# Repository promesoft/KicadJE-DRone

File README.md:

# Kicad-droneosc
This is a very simple circuit based around S9018 NPN BJT's.

It creates a saw pulse and in this config I can modulate them via the base of the BJT. Its inspired by the work of [Kerry Wong](http://www.kerrywong.com/2014/03/19/bjt-in-reverse-avalanche-mode/) and [Sam Battle](https://www.lookmumnocomputer.com/projects/#/simplest-oscillator/)

## Reverse Avalanche Breakdown
As this oscilator is based on reverse avalanche breakdown it is highly dependent on the type of BJT used. For this setup the SS9018 high frequency transistor has been selected as it start oscilating below 9V (which is often used in stomp box effect pedals). 
For more details on this oscilator visit [AN47](https://www.analog.com/media/en/technical-documentation/application-notes/an47fa.pdf)

## Status - Rev A board - initial verification
### Initial 
| Stage  | Detail | Status |
| ------------- | ------------- | ------------- |
| create material  | sch/pcb | produced Rev A  |
| | gerber | produced and uploaded RevA |
| production  | ordered  | OK |
|  | produced | OK |
|  | delivered | OK |
### Preliminary validation
| Test  | Detail | Status |
| ------------- | ------------- | ------------- |
| Initial Inspection | Visual | See Errata |
| | Component Mounting | OK LFO 2|
| Initial Technical Test | LFO 1 |  |
| | OSC 1 |  |
| | LFO 2 | OK |
| | OSC 1 |  |

### Secondary validation
| Test  | Detail | Status |
| ------------- | ------------- |------------- |
| Product Test | LFO 1 |  |
| | OSC 1 |  |
| | LFO 2  | OSC+AM OK - Volume ok (see Errata)|
| | OSC 1 |  |
| Physical | 1590 II Box |  |
|  | Eurorack |  |
| Long Term Product Test | | ongoing |
### Errata
 - Footprint of mini jacks should be updated
 - Assisting text on potmeters
 - D1 is 0805 - should have been SOD123 or Minimelf
 - RV7 Volume Pot is reversed (possibly all other vol pots)
 - 10uf used for LFO output capacitor
  
### Issues and Notes

## Physical Construction
 - 50,8x100,2mm
 - Optional cut in 2 
 - Mounting in either Eurorack or Stompbox 1590B

## Vital Components
 - Jack connectors: PJ-321 (important for the footprint)
 - SS9018 HJ NPN BJT for the oscillator (important for the voltage)
 - 5516 LDR for the vactrol (matched with the pot for the osc)

## Features
4 Separate saw oscillators.
 - 2 identical
 - 1 simple
 - 1 with VCO (Vactrol) and Modulation input

## Modulation
### AM
Each section of the oscilators are AC coupled with a reasonably high input resistance that in the prototype enabled cascading of the oscilators so the output of the oscilator would be AM mulated with the input on the base.
### CV / FM / Vactrol
Prototype has been performed with a GL5516 LDR in a heat shrink package with an LED - its not exactly 1V/Oct but it works

# Prototype implementation
A simple stripboard implementation in a 1590B stompbox

# 3D 
Visualization of the board

## LFO 1 and OSC 1 3D

# LFO 1 Schematic

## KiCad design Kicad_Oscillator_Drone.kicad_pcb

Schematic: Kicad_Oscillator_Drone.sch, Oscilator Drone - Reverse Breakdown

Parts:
C1: 100u; CP_Radial_D6.3mm_P2.50mm
C2, C8: 680n; C_0805_2012Metric_Pad1.15x1.40mm_HandSolder
C3: 220u; CP_Radial_D7.5mm_P2.50mm
C4, C10: 470n; C_0805_2012Metric_Pad1.15x1.40mm_HandSolder
C5, C11: 220n; C_0805_2012Metric_Pad1.15x1.40mm_HandSolder
C6: 4u7; C_0805_2012Metric_Pad1.15x1.40mm_HandSolder
C7, C13: 1u; C_0805_2012Metric_Pad1.15x1.40mm_HandSolder
C9: 100u; CP_Radial_D7.5mm_P2.50mm
C12: 2u2; C_0805_2012Metric_Pad1.15x1.40mm_HandSolder
D1: 9v; D_0805_2012Metric_Pad1.15x1.40mm_HandSolder
D2: red; LED_D3.0mm
D3: OSC1CV; LED_D3.0mm
J1, J2: Power Out; TerminalBlock_Phoenix_PT-3.5mm_2pol
J3: Jack-DC; BarrelJack_CUI_PJ-063AH_Horizontal
J4: OSC1CV; AudioJack3StereoNarrow-PJ-321
J7: LFO1 Power; TerminalBlock_Phoenix_PT-3.5mm_2pol
J8, J10, J11, J12, J14, J15, J17: AudioJack; AudioJack3StereoNarrow-PJ-321
Q1, Q2, Q3, Q4: S9018; SOT-23_Handsoldering
R1, R2, R6, R7: 1k; R_0805_2012Metric_Pad1.15x1.40mm_HandSolder
R3: 680R; R_0805_2012Metric_Pad1.15x1.40mm_HandSolder
R4, R5, R8, R9: 47k; R_0805_2012Metric_Pad1.15x1.40mm_HandSolder
R10, R12: 1k2; R_0805_2012Metric_Pad1.15x1.40mm_HandSolder
R11: OSC1CV; R_LDR_10x8.5mm_P7.6mm_Vertical
RV1, RV2, RV5, RV6: 10k; Potentiometer_Piher_T-16H_Single_Horizontal
RV3, RV4, RV7, RV8: 100k; Potentiometer_Piher_T-16H_Single_Horizontal
TP1: OSC1CV; Pin_D1.0mm_L10.0mm_LooseFit
TP5: LFO1AM; Pin_D1.0mm_L10.0mm_LooseFit
TP6: LFO1; Pin_D1.0mm_L10.0mm_LooseFit
TP7: LFO2AM; Pin_D1.0mm_L10.0mm_LooseFit
TP8: LFO2; Pin_D1.0mm_L10.0mm_LooseFit
TP9: OSC1AM; Pin_D1.0mm_L10.0mm_LooseFit
TP14: OSC1; Pin_D1.0mm_L10.0mm_LooseFit
TP15: OSC2AM; Pin_D1.0mm_L10.0mm_LooseFit
TP16: OSC2; Pin_D1.0mm_L10.0mm_LooseFit

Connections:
+10V: D1.1, J1.1, J2.1, J7.1, R1.1, R2.1, R3.1, R6.1, R7.1, R10.2
/DC_in: C1.1, J3.1, R3.2
/LFO1: C3.1, Q1.2, RV1.3, RV3.1
/LFO2: C9.1, Q3.2, RV5.3, RV7.1
/OSC1: C6.1, Q2.2, R11.2, RV2.3, RV4.1
/OSC1_CV: J4.T, R12.2, TP1.1
/OSC2: C12.1, Q4.2, RV6.3, RV8.1
GND: C1.2, C3.2, C6.2, C9.2, C12.2, D1.2, D2.1, J1.2, J2.2, J3.2, J7.2, J8.R, J8.S, J10.R, J10.S, J11.R, J11.S, J12.R, J12.S, J14.R, J14.S, J15.R, J15.S, J17.R, J17.S, Q1.3, Q2.3, Q3.3, Q4.3, RV3.3, RV4.3, RV7.3, RV8.3
LFO1-AM: C2.2, TP5.1
LFO1-OUT: C4.1, J8.T, TP6.1
LFO2-AM: C8.2, J10.T, TP7.1
LFO2-OUT: C10.1, J11.T, TP8.1
unnamed: C2.1, R4.1
unnamed: C4.2, RV3.2
unnamed: C5.1, R5.1
unnamed: C7.2, RV4.2
unnamed: C8.1, R8.1
unnamed: C10.2, RV7.2
unnamed: C11.1, R9.1
unnamed: C13.2, RV8.2
unnamed: D2.2, R10.1
unnamed: D3.1, J4.R, J4.S
unnamed: D3.2, R12.1
unnamed: Q1.1, R4.2
unnamed: Q2.1, R5.2
unnamed: Q3.1, R8.2
unnamed: Q4.1, R9.2
unnamed: R1.2, RV1.1, RV1.2
unnamed: R6.2, RV5.1, RV5.2
unnamed: R7.2, RV6.1, RV6.2
unnamed: R2.2, R11.1, RV2.1, RV2.2
OSC1-AM: C5.2, J12.T, TP9.1
OSC1-OUT: C7.1, J14.T, TP14.1
OSC2-AM: C11.2, J15.T, TP15.1
OSC2-OUT: C13.1, J17.T, TP16.1

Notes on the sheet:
PSU
OSC 1
OSC 2
LFO 1
LFO 2
Connectors

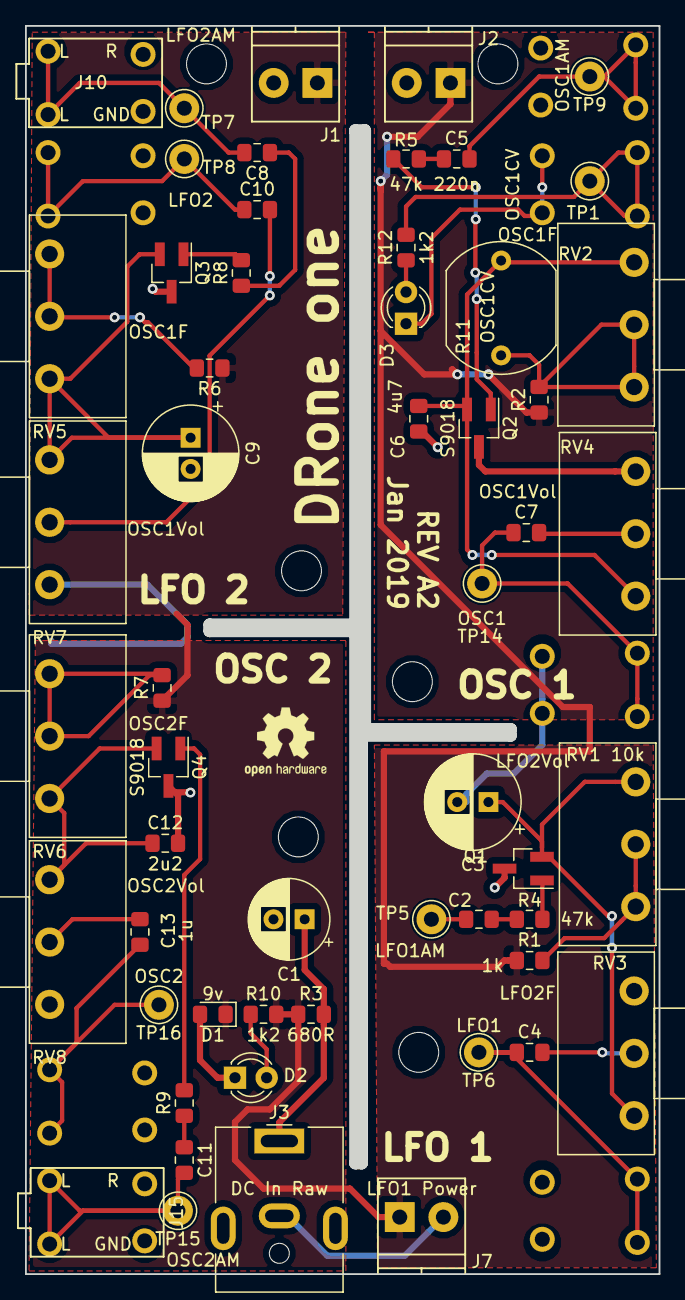
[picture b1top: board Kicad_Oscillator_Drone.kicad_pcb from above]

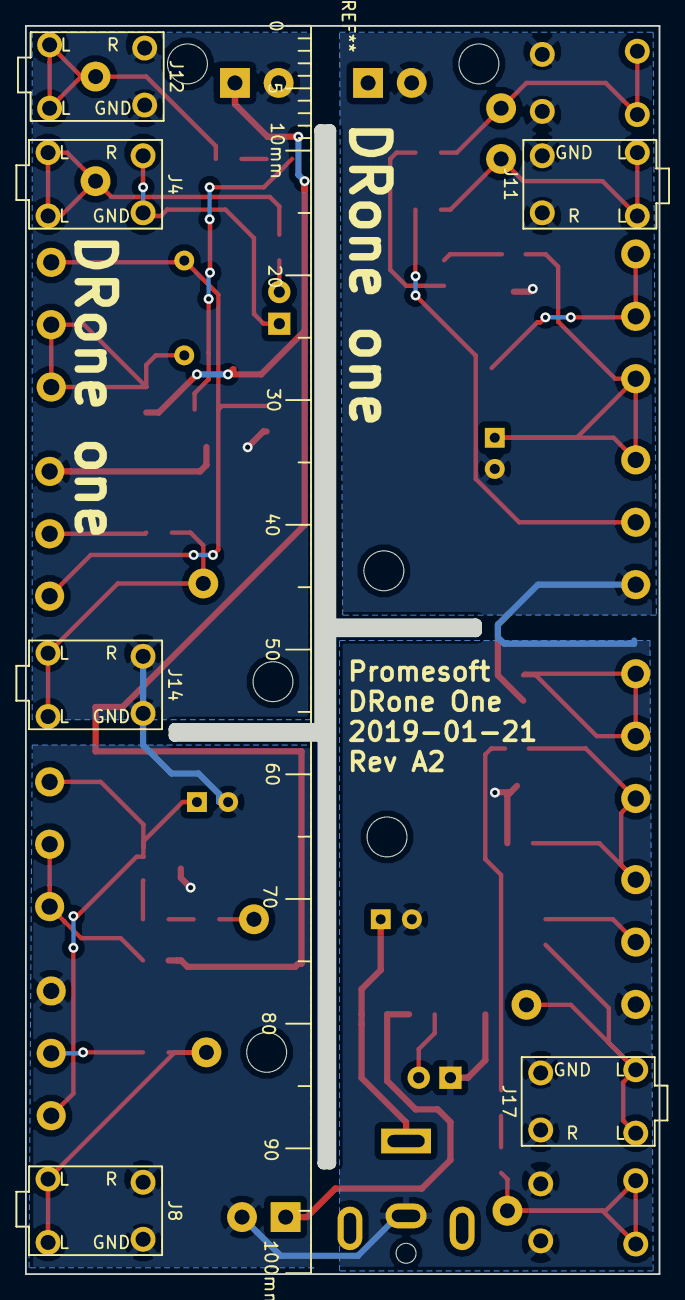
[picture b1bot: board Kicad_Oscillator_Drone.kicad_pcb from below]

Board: 2 copper layers, 50.0 x 99.2 mm, 61 parts (6 on the bottom side), 35 nets.

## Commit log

2018-12-14 Import Local Project
    Halfway to laying out dual print with an LFO and an OSC on each part of the board
2018-12-14 prefix
    prefix
2018-12-14 Pict
    Pictures of drone rel
2018-12-14 Removed connectort
    Connectors and testpoints removed.
2018-12-14 Vactrol and pwr fix
    Power fix and alteration
    Remove LFO1 AM
    Add Vactrol to OSC1
    Net names
2018-12-15 3D Updated
    3D Models
2018-12-15 Update README.md
    Sam Battle inspiration
2018-12-15 Routing started LFO2 OSC1
2018-12-15 Rev A done
    Ground planes
    Mounting holes
    DRC
    Labels
2018-12-16 Gerber
    Gerber output added for JLC
2018-12-17 README w Schematic
    update readme
2018-12-18 Update README.md
    3D
2018-12-19 Update README.md
    Headlines....
2018-12-20 Update README.md
    Reverse avalanche
2018-12-25 Vactrol pic
    Vactrol on OSC1
2018-12-25 Update README.md
    vactrol osc1
2019-01-15 3D Rev A
2019-01-21 Rev A2 - Text and Jack footprint update
2019-01-21 RevA Cleanup
